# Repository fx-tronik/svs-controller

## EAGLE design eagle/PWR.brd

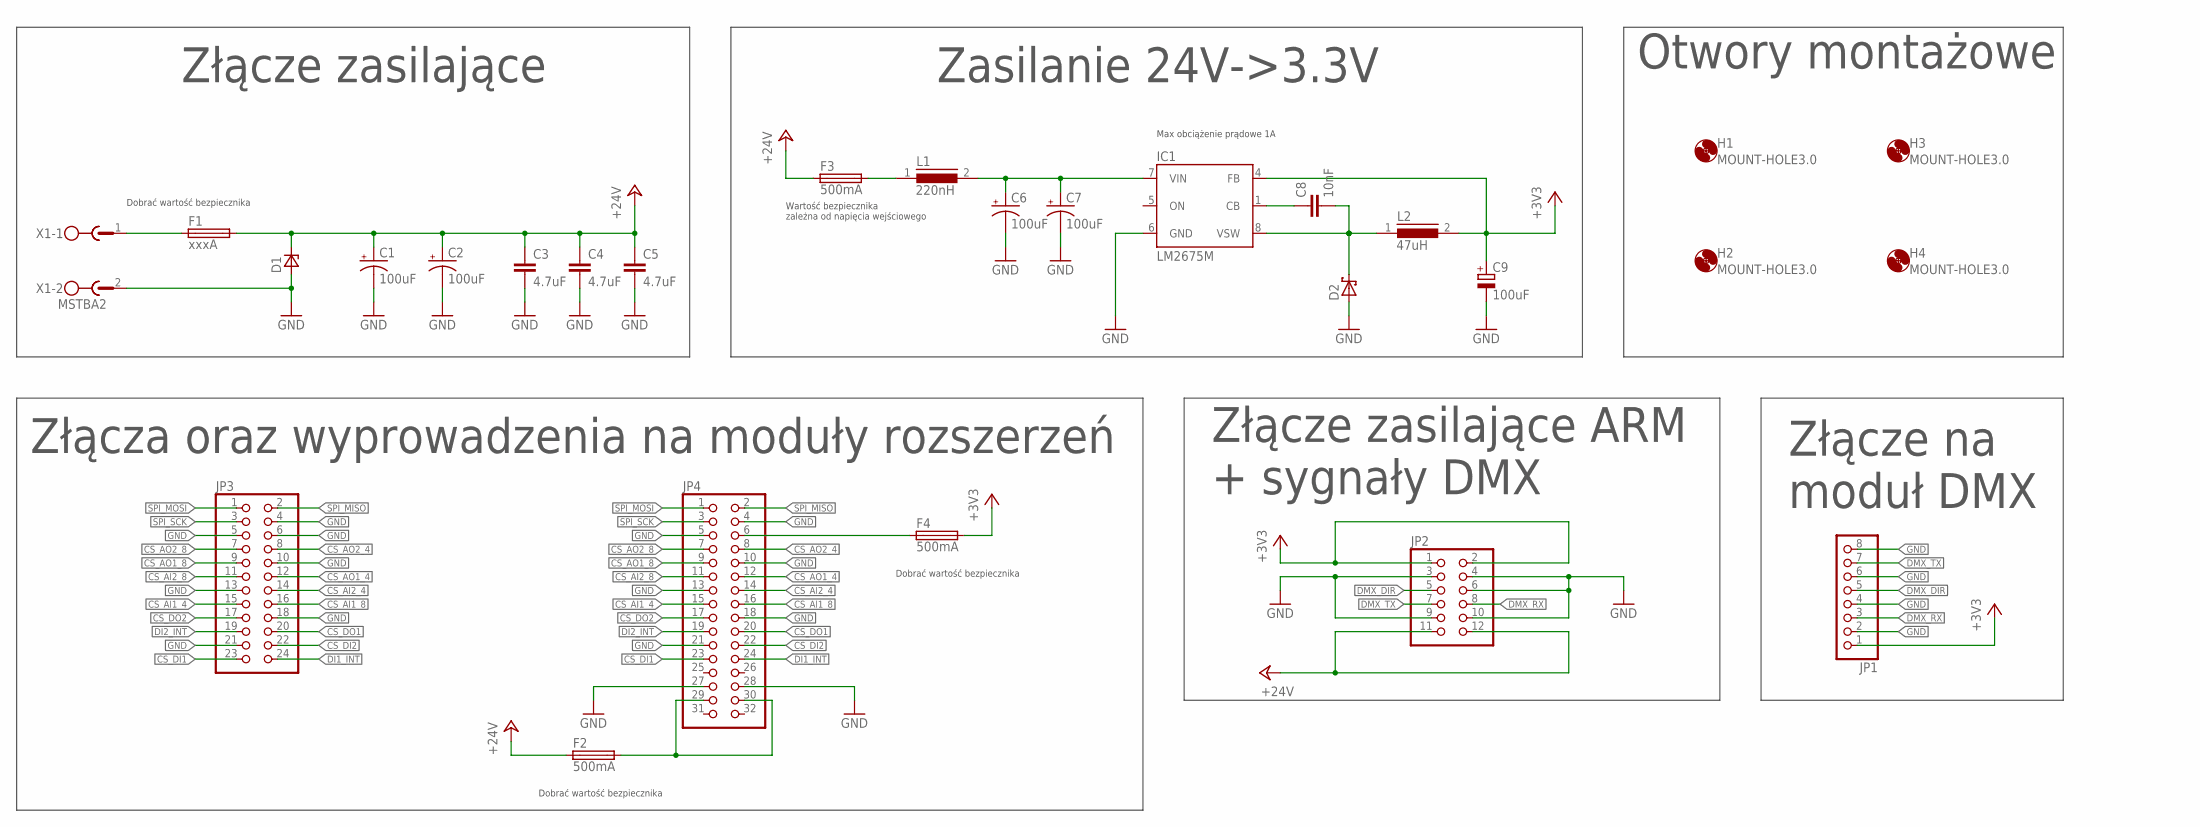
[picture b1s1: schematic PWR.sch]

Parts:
C1, C2, C6, C7: 100uF; TT5D10; MPN UPJ1H101MPD6
C3, C4, C5: 4.7uF; C0805; MPN GRM21BR61H475ME51L
C8: 10nF; C0603; MPN 06035C103KAT2A
C9: 100uF; SMC_C; MPN TAJC107K010TNJ
D1: P6SMB20A; SMB_A; MPN TPSMB24A-VR
D2: SCHOTTKY-DIODESMD; SMB; MPN SS26T3G
F1: xxxA; TR5; MPN 56000001009
F2, F3, F4: 500mA; TR5; MPN 56000001009
H1, H2, H3, H4: MOUNT-HOLE3.0; 3,0
IC1: LM2675M; SO08; MPN LM2675MX-3.3/NOPB
JP1: PINHD-1X8/90; 1X08/90; MPN DS1024-1*8R0
JP2: PINHD-2X6; 2X06; MPN DS1023-2*6S21
JP3: PINHD-2X12; 2X12; MPN DS1023-2*12S21
JP4: PINHD-2X16/90; 2X16/90; MPN DS1024-2*16R0
L1: 220nH; 7.3X6.3; MPN SRP7028A-R22Y
L2: 47uH; 12.5X12.5; MPN SRR1280-470M
X1: MSTBA2; MPN 2EDGRC-5.08-02P-14-00A(H)

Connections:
+3V3: C9.+, F4.2, IC1.4 (FB), JP1.1, JP2.1, JP2.2, L2.2
+24V: C1.+, C2.+, C3.1, C4.1, C5.1, D1.C, F1.2, F2.1, F3.1, JP2.11, JP2.12
CS_AI1_4: JP3.15, JP4.15
CS_AI1_8: JP3.16, JP4.16
CS_AI2_4: JP3.14, JP4.14
CS_AI2_8: JP3.11, JP4.11
CS_AO1_4: JP3.12, JP4.12
CS_AO1_8: JP3.9, JP4.9
CS_AO2_4: JP3.8, JP4.8
CS_AO2_8: JP3.7, JP4.7
CS_DI1: JP3.23, JP4.23
CS_DI2: JP3.22, JP4.22
CS_DO1: JP3.20, JP4.20
CS_DO2: JP3.17, JP4.17
DI1_INT: JP3.24, JP4.24
DI2_INT: JP3.19, JP4.19
DMX_DIR: JP1.5, JP2.5
DMX_RX: JP1.3, JP2.8
DMX_TX: JP1.7, JP2.7
GND: C1.-, C2.-, C3.2, C4.2, C5.2, C6.-, C7.-, C9.-, D1.A, D2.A, IC1.6 (GND), JP1.2, JP1.4, JP1.6, JP1.8, JP2.3, JP2.4, JP2.6, JP2.9, JP2.10, JP3.4, JP3.5, JP3.6, JP3.10, JP3.13, JP3.18, JP3.21, JP4.4, JP4.5, JP4.10, JP4.13, JP4.18, JP4.21, JP4.27, JP4.28, X1.2
unnamed: F1.1, X1.1
unnamed: F4.1, JP4.6
unnamed: F2.2, JP4.29, JP4.30
unnamed: F3.2, L1.1
unnamed: C8.1, IC1.1 (CB)
SPI_MISO: JP3.2, JP4.2
SPI_MOSI: JP3.1, JP4.1
SPI_SCK: JP3.3, JP4.3
VIN: C6.+, C7.+, IC1.7 (VIN), L1.2
VSW: C8.2, D2.C, IC1.8 (VSW), L2.1

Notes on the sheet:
Dobrać wartość bezpiecznika
Max obciążenie prądowe 1A
Wartość bezpiecznika zależna od napięcia wejściowego
Zasilanie 24V->3.3V
Złącze zasilające
Złącze na moduł DMX
Złącze zasilające ARM + sygnały DMX
Otwory montażowe
Złącza oraz wyprowadzenia na moduły rozszerzeń

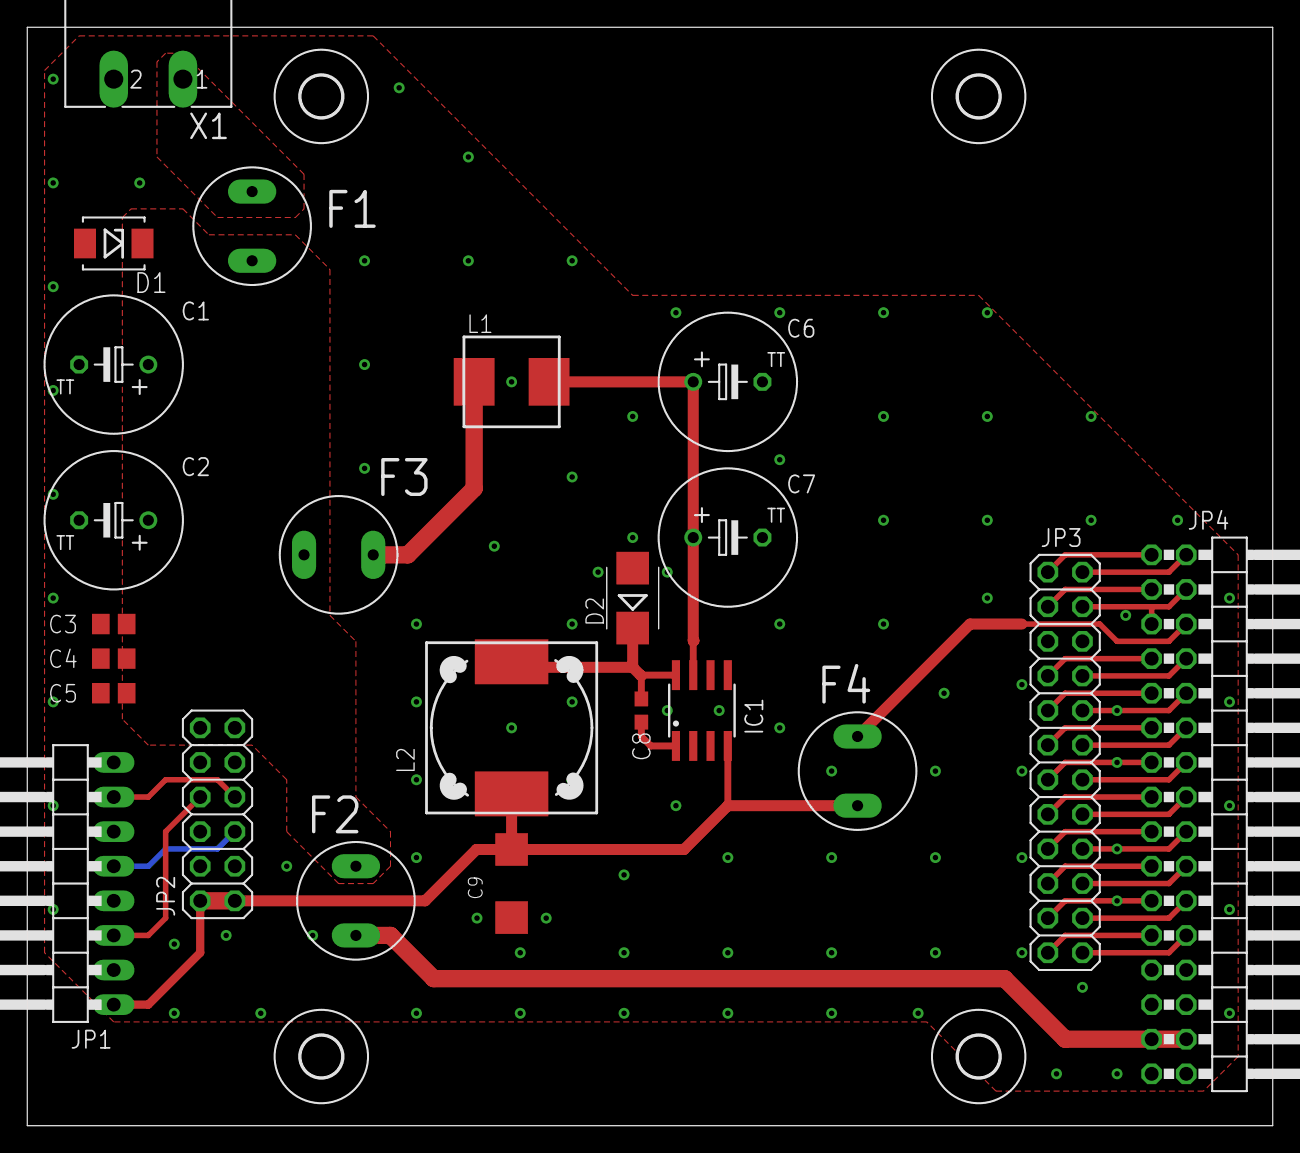
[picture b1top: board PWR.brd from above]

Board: 2 copper layers, 91.4 x 80.6 mm, 27 parts (0 on the bottom side), 30 nets.

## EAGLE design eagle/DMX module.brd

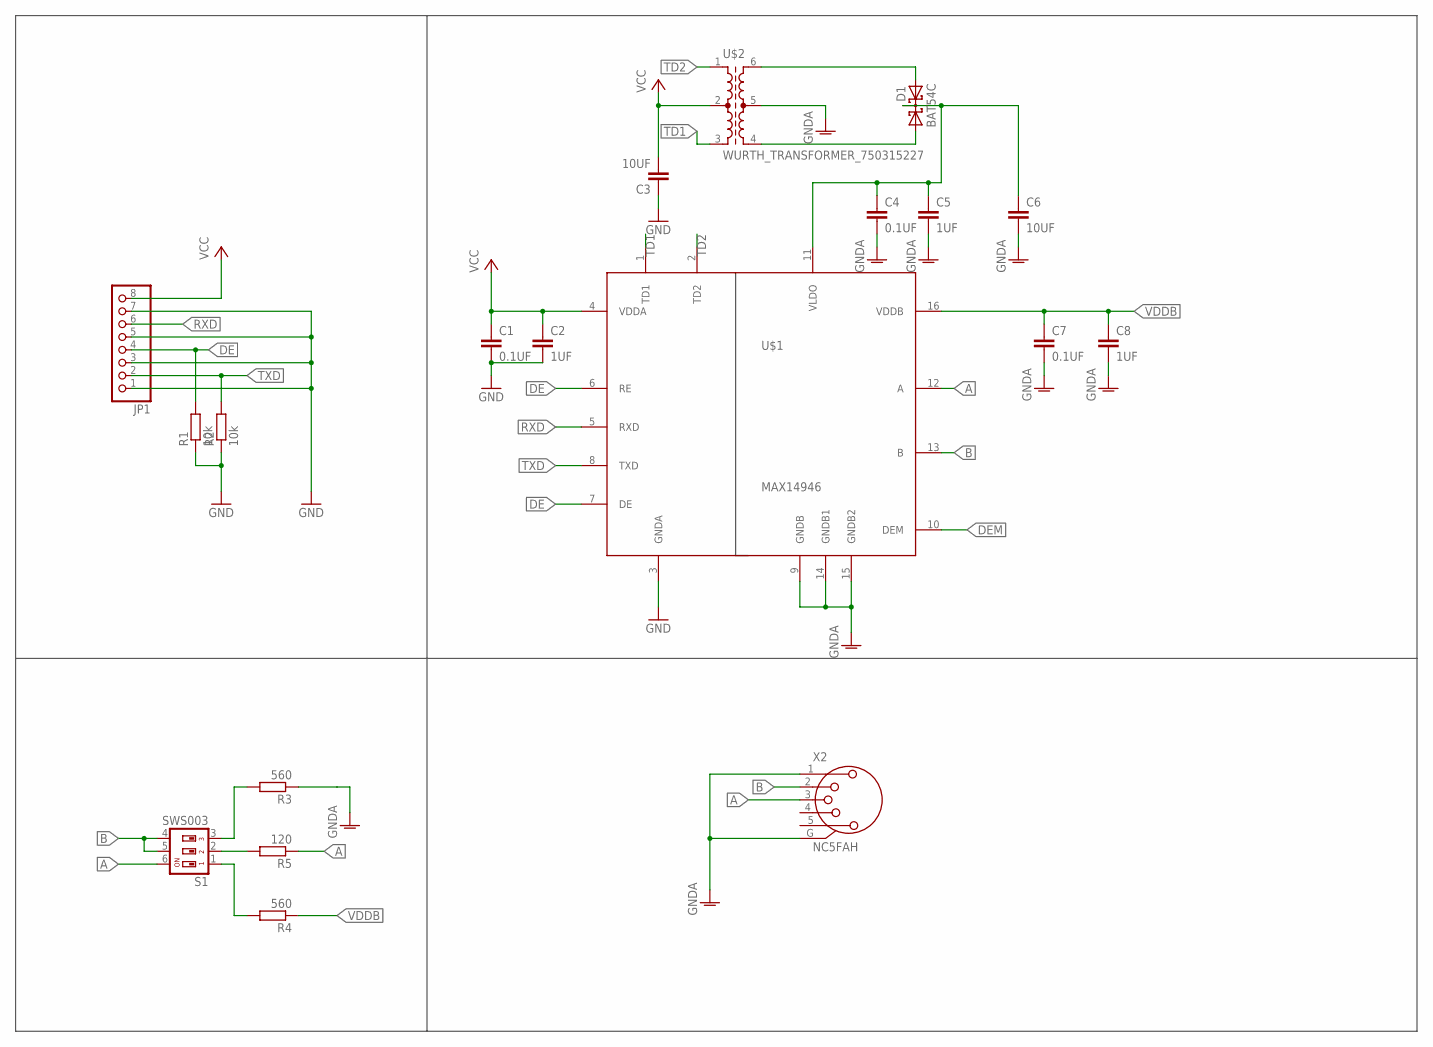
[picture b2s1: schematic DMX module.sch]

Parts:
C1, C4, C7: 0.1UF; C0603; MPN 06033C104KAT2A
C2, C5, C8: 1UF; C0603; MPN 0603YC105KAT4A
C3, C6: 10UF; C0805; MPN 08056G106ZAT2A
D1: BAT54C; SOT23; MPN 755-BAT54AHMFHT116
JP1: PINHD-1X8/90; 1X08/90; MPN DS1022-1*20RDF1-1
R1, R2: 10k; R0603; MPN RC0603JR-0710KA
R3, R4: 560; R0603; MPN RC0603FR-13560RL
R5: 120; R0603; MPN RC0603FR-10120RL
S1: SWS003; SMS-003; MPN 774-2193MST
U$1: MAX14946; SOIC16W; MPN 700-MAX14946EWE+
U$2: WURTH_TRANSFORMER_750315227; WURTH750315227; MPN 710-750315227
X2: NC5FAH

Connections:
A: R5.1, S1.6, U$1.12 (A), X2.3
B: S1.4, S1.5, U$1.13 (B), X2.2
DE: JP1.4, R1.2, U$1.6 (RE), U$1.7 (DE)
DEM: U$1.10 (DEM)
GND: C1.2, C2.2, C3.1, JP1.1, JP1.3, JP1.5, JP1.7, R1.1, R2.1, U$1.3 (GNDA)
GNDA: C4.2, C5.2, C6.2, C7.2, C8.2, R3.1, U$1.9 (GNDB), U$1.14 (GNDB1), U$1.15 (GNDB2), U$2.5, X2.1, X2.G
unnamed: R5.2, S1.2
unnamed: R4.2, S1.1
unnamed: D1.1 (A1), U$2.4
unnamed: D1.2 (A2), U$2.6
unnamed: C4.1, C5.1, C6.1, D1.3 (CC), U$1.11 (VLDO)
unnamed: R3.2, S1.3
RXD: JP1.6, U$1.5 (RXD)
TD1: U$1.1 (TD1), U$2.3
TD2: U$1.2 (TD2), U$2.1
TXD: JP1.2, R2.2, U$1.8 (TXD)
VCC: C1.1, C2.1, C3.2, JP1.8, U$1.4 (VDDA), U$2.2
VDDB: C7.1, C8.1, R4.1, U$1.16 (VDDB)

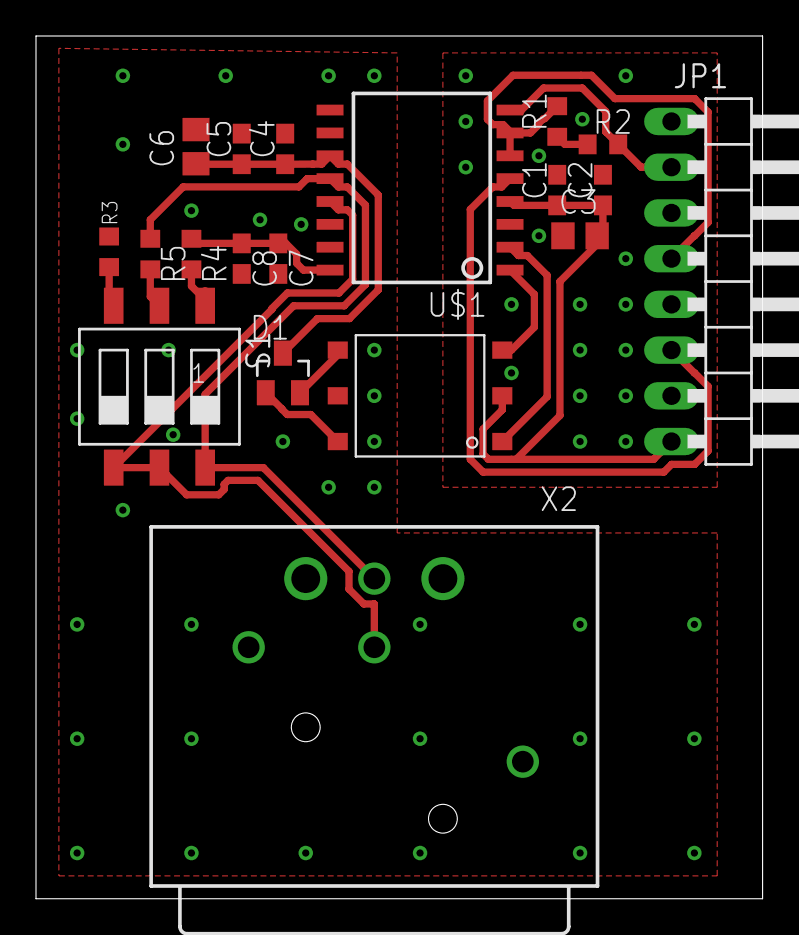
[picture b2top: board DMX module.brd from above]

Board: 2 copper layers, 40.4 x 47.9 mm, 19 parts (0 on the bottom side), 17 nets.

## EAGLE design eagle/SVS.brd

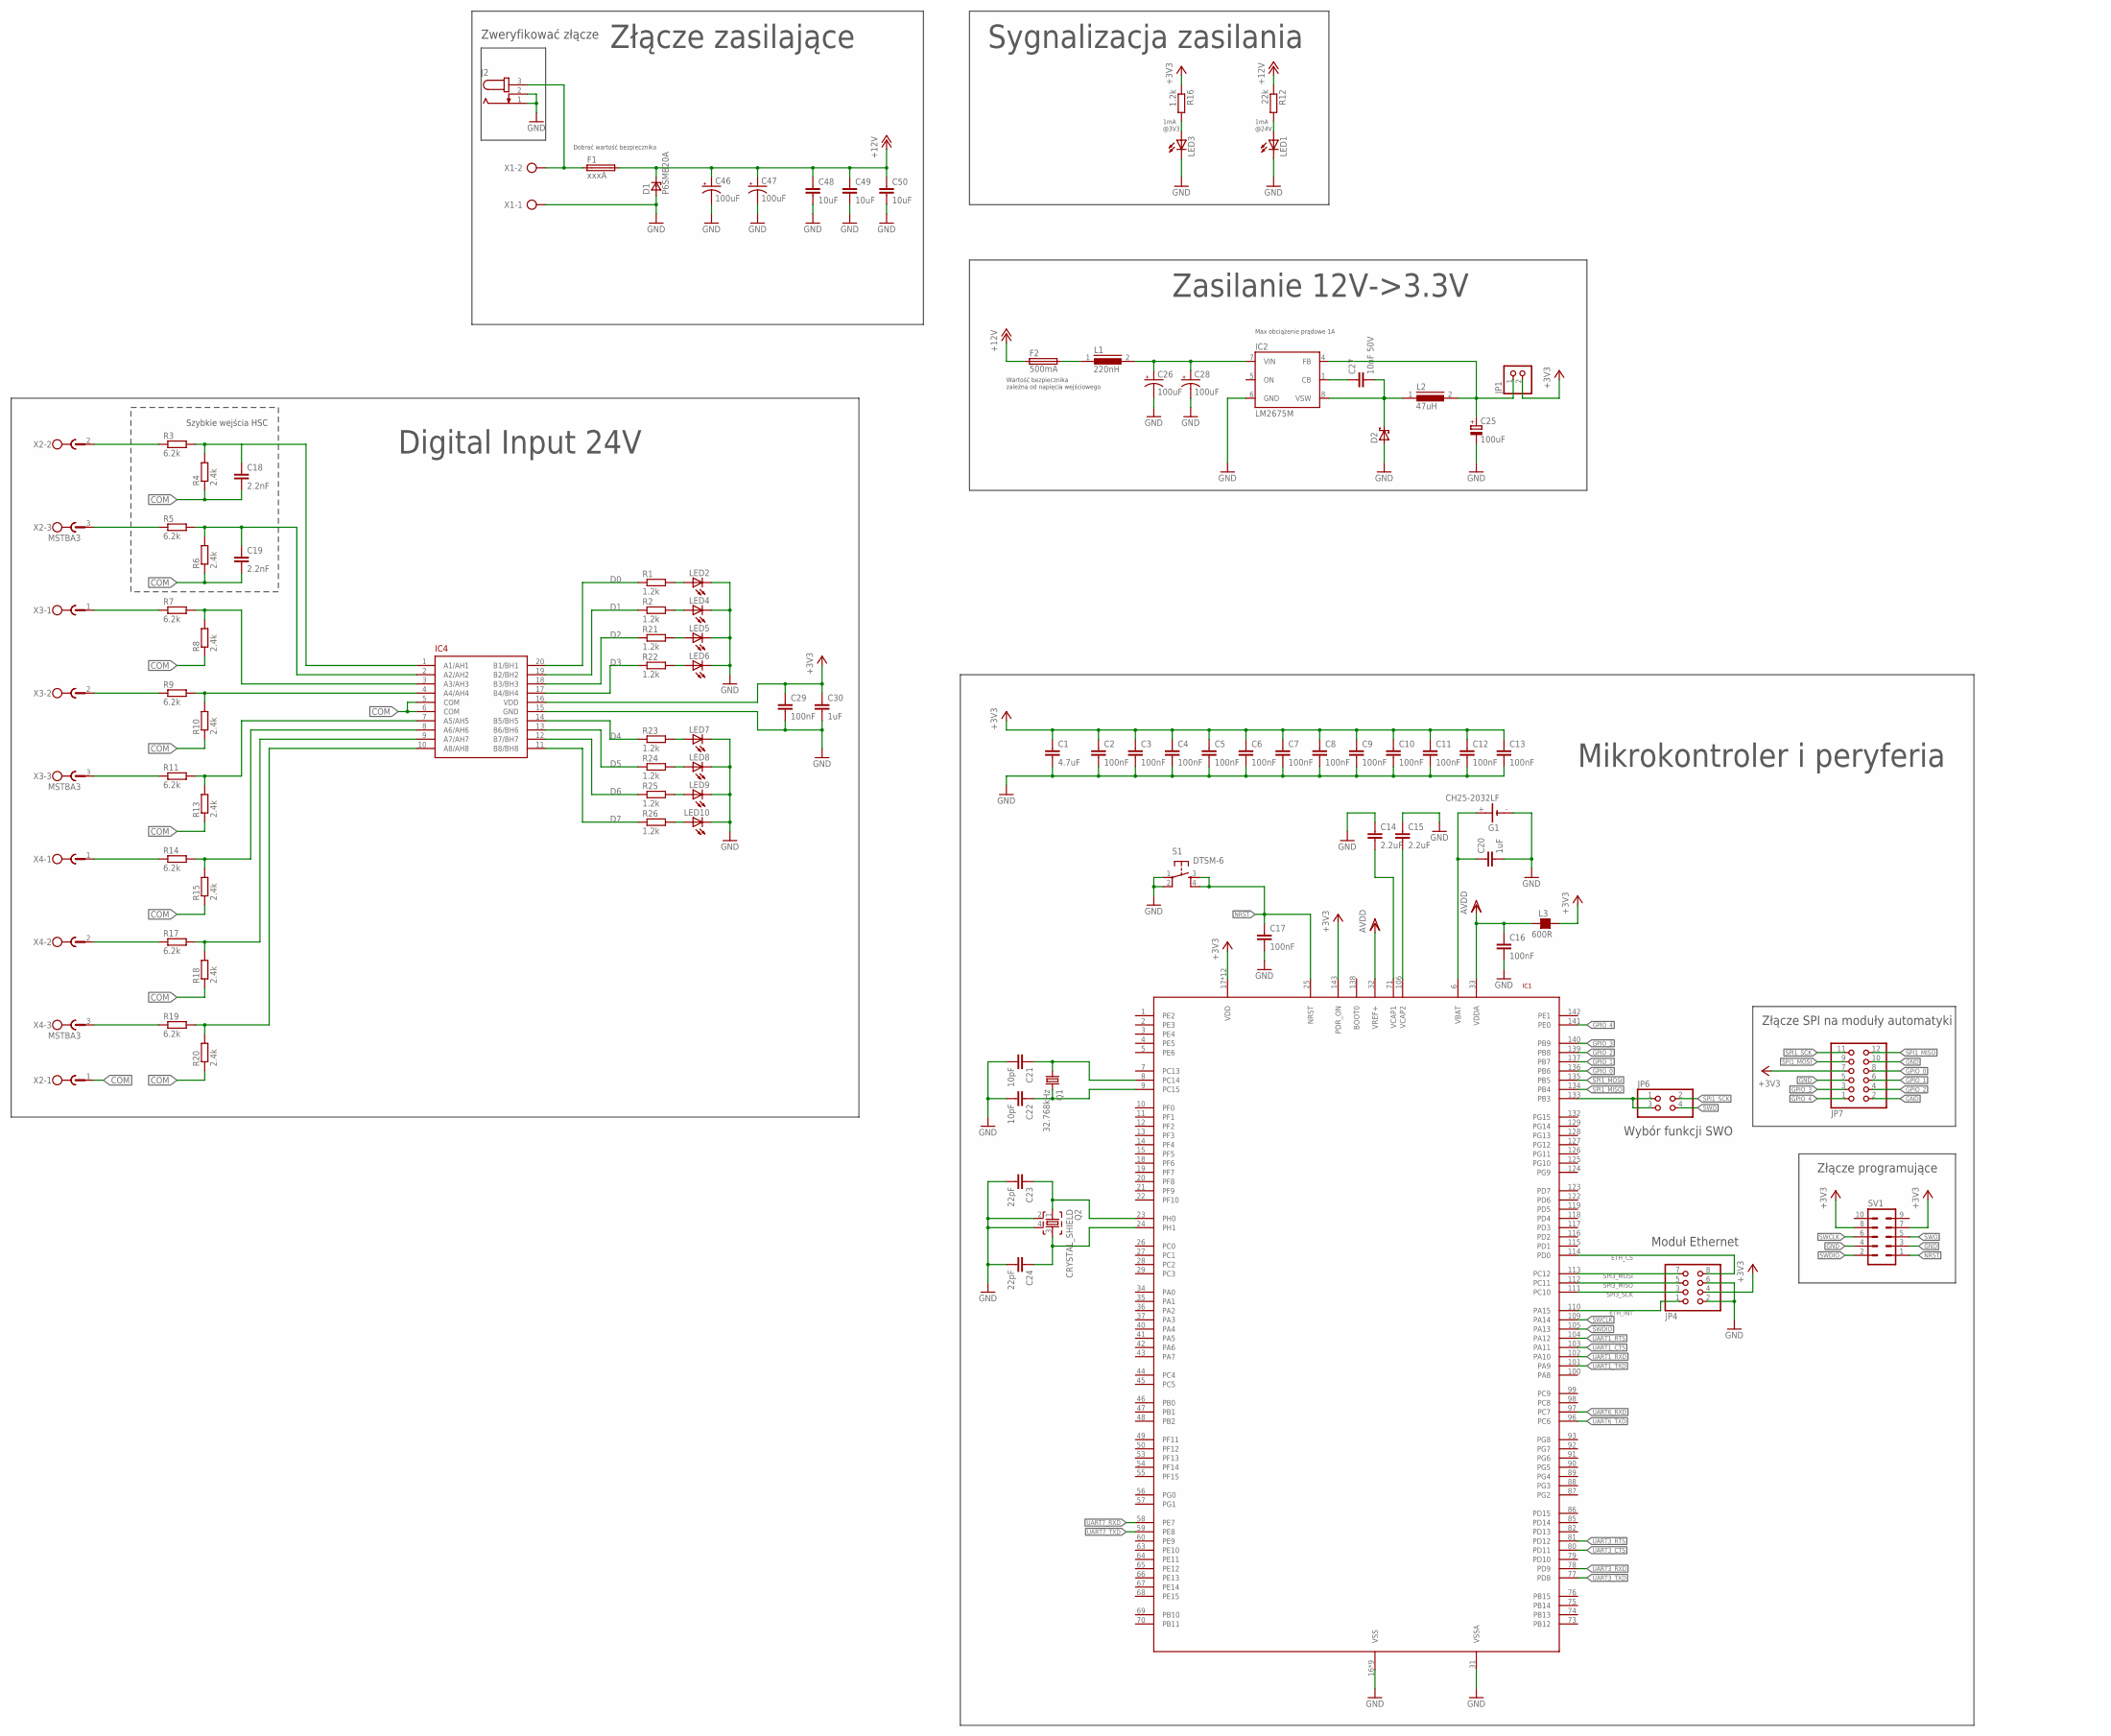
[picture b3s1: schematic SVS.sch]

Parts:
C1: 4.7uF; C0603K; MPN 0603ZD475KAT2A
C2, C3, C4, C5, C6, C7, C8, C9, C10, C11, C12, C13, C16, C17, C29: 100nF; C0603K; MPN 06033C104KAT2A
C14, C15: 2.2uF; C0603K; MPN 06036C225KAT2A
C18, C19: 2.2nF; C0805; MPN 06035C222JAT2A
C20, C30: 1uF; C0603K; MPN 0603YC105KAT4A
C21, C22: 10pF; C0603K; MPN 06035A100JAT2A
C23, C24: 22pF; C0603K; MPN 06035A220JAT2A
C25: 100uF; SMC_C; MPN TAJC107K010TNJ
C26, C28, C46, C47: 100uF; UD-8X10_NICHICON; MPN UCD1H101MNL1GS
C27: 10nF 50V; C0603; MPN 06035C103KAT2A
C48, C49, C50: 10uF; C0805; MPN GRM21BR6YA106KE43L
D1: P6SMB20A; SMB_A; MPN TPSMB24A-VR
D2: SCHOTTKY-DIODESMD; SMB; MPN SS26T3G
F1: xxxA; TR5
F2: 500mA; TR5
G1: CH25-2032LF; MPN CH25-2032
IC1: STM32F429ZILQFP144; LQFP144; MPN STM32F429ZIT6
IC2: LM2675M; SO08; MPN LM2675MX-3.3/NOPB
IC4: SI838X; QSOP-20; MPN SI8382P-IU
J2: JACK-PLUG1; SPC4078
JP1: PINHD-1X2; 1X02
JP4: PINHD-2X4; 2X04
JP6: PINHD-2X2; 2X02
JP7: PINHD-2X6/90; 2X06/90
L1: 220nH; 7.3X6.3; MPN SRP7028A-R22Y
L2: 47uH; 12.5X12.5; MPN SRR1280-470M
L3: 600R; L0603; MPN MMZ1608S601ATD25
LED1, LED3: LEDCHIP-LED0603; CHIP-LED0603; MPN APTD1608LSURCK
LED2, LED4, LED5, LED6, LED7, LED8, LED9, LED10: LEDCHIP-LED0603; CHIP-LED0603; MPN APTD1608LCGCK
Q1: 32.768kHz; CRYSTAL_3.5X1.5; MPN ECS-.327-9-34QCS-TR
Q2: CRYSTAL_SHIELD; CRYSTAL_5X3.2; MPN LFXTAL059158
R1, R2, R16, R21, R22, R23, R24, R25, R26: 1.2k; R0603; MPN RC0603FR-071K2L
R3, R5, R7, R9, R11, R14, R17, R19: 6.2k; R1206; MPN RC1206JR-076K2L
R4, R6, R8, R10, R13, R15, R18, R20: 2.4k; R1206; MPN RC1206JR-072K4L
R12: 22k; R0603; MPN RC0603FR-0722KL
S1: DTSM-6; MPN DTSM-63N-V-B
SV1: ML10
X1: AK300/2
X2, X3, X4: MSTBA3

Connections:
+3V3: C1.1, C2.1, C3.1, C4.1, C5.1, C6.1, C7.1, C8.1, C9.1, C10.1, C11.1, C12.1, C13.1, C29.1, C30.1, IC1.17 (VDD), IC1.30 (VDD), IC1.39 (VDD), IC1.52 (VDD), IC1.62 (VDD), IC1.72 (VDD), IC1.84 (VDD), IC1.95 (VDD), IC1.108 (VDD), IC1.121 (VDD), IC1.131 (VDD), IC1.143 (PDR_ON), IC1.144 (VDD), IC4.16 (VDD), JP1.2, JP4.4, JP7.7, L3.2, R16.1, SV1.7, SV1.8
+12V: C46.+, C47.+, C48.1, C49.1, C50.1, D1.C, F1.2, F2.1, R12.1
AVDD: IC1.32 (VREF+)
COM: C18.2, C19.2, IC4.5 (COM), IC4.6 (COM), R4.1, R6.1, R8.1, R10.1, R13.1, R15.1, R18.1, R20.1, X2.1
D0: IC4.20 (B1/BH1), R1.1
D1: IC4.19 (B2/BH2), R2.1
D2: IC4.18 (B3/BH3), R21.1
D3: IC4.17 (B4/BH4), R22.1
D4: IC4.14 (B5/BH5), R23.1
D5: IC4.13 (B6/BH6), R24.1
D6: IC4.12 (B7/BH7), R25.1
D7: IC4.11 (B8/BH8), R26.1
ETH_CS: IC1.114 (PD0), JP4.8
ETH_INT: IC1.110 (PA15), JP4.1
GND: C1.2, C2.2, C3.2, C4.2, C5.2, C6.2, C7.2, C8.2, C9.2, C10.2, C11.2, C12.2, C13.2, C14.1, C15.1, C16.2, C17.2, C20.2, C21.2, C22.2, C23.2, C24.2, C25.-, C26.-, C28.-, C29.2, C30.2, C46.-, C47.-, C48.2, C49.2, C50.2, D1.A, D2.A, G1.-, IC1.16 (VSS), IC1.31 (VSSA), IC1.38 (VSS), IC1.51 (VSS), IC1.61 (VSS), IC1.83 (VSS), IC1.94 (VSS), IC1.107 (VSS), IC1.120 (VSS), IC1.130 (VSS), IC2.6 (GND), IC4.15 (GND), J2.1, J2.2, JP4.2, JP4.6, JP7.2, JP7.5, JP7.10, LED1.C, LED2.C, LED3.C, LED4.C, LED5.C, LED6.C, LED7.C, LED8.C, LED9.C, LED10.C, Q2.2, Q2.4, S1.1, S1.2, SV1.3, SV1.4, X1.1
GPIO_0: IC1.136 (PB6), JP7.8
GPIO_1: IC1.137 (PB7), JP7.6
GPIO_2: IC1.139 (PB8), JP7.4
GPIO_3: IC1.140 (PB9), JP7.3
GPIO_4: IC1.141 (PE0), JP7.1
unnamed: F1.1, J2.3, X1.2
unnamed: C14.2, IC1.71 (VCAP1)
unnamed: C15.2, IC1.106 (VCAP2)
unnamed: C21.1, IC1.8 (PC14), Q1.1
unnamed: C22.1, IC1.9 (PC15), Q1.2
unnamed: IC1.133 (PB3), JP6.1, JP6.3
unnamed: C23.1, IC1.23 (PH0), Q2.1
unnamed: C24.1, IC1.24 (PH1), Q2.3
unnamed: C18.1, IC4.1 (A1/AH1), R3.2, R4.2
unnamed: F2.2, L1.1
unnamed: LED2.A, R1.2
unnamed: C19.1, IC4.2 (A2/AH2), R5.2, R6.2
unnamed: LED4.A, R2.2
unnamed: LED5.A, R21.2
unnamed: R3.1, X2.2
unnamed: C27.1, IC2.1 (CB)
unnamed: LED6.A, R22.2
unnamed: R5.1, X2.3
unnamed: IC4.3 (A3/AH3), R7.2, R8.2
unnamed: R7.1, X3.1
unnamed: IC4.4 (A4/AH4), R9.2, R10.2
unnamed: R9.1, X3.2
unnamed: IC4.7 (A5/AH5), R11.2, R13.2
unnamed: R11.1, X3.3
unnamed: IC4.8 (A6/AH6), R14.2, R15.2
unnamed: R14.1, X4.1
unnamed: IC4.9 (A7/AH7), R17.2, R18.2
unnamed: R17.1, X4.2
unnamed: IC4.10 (A8/AH8), R19.2, R20.2
unnamed: R19.1, X4.3
unnamed: LED1.A, R12.2
unnamed: LED7.A, R23.2
unnamed: LED8.A, R24.2
unnamed: LED9.A, R25.2
unnamed: LED10.A, R26.2
unnamed: C25.+, IC2.4 (FB), JP1.1, L2.2
unnamed: LED3.A, R16.2
NRST: C17.1, IC1.25 (NRST), S1.3, S1.4, SV1.1
SPI1_MISO: IC1.134 (PB4), JP7.12
SPI1_MOSI: IC1.135 (PB5), JP7.9
SPI1_SCK: JP6.2, JP7.11
SPI3_MISO: IC1.112 (PC11), JP4.5
SPI3_MOSI: IC1.113 (PC12), JP4.7
SPI3_SCK: IC1.111 (PC10), JP4.3
SWCLK: IC1.109 (PA14), SV1.6
SWDIO: IC1.105 (PA13), SV1.2
SWO: JP6.4, SV1.5
UART1_CTS: IC1.103 (PA11)
UART1_RTS: IC1.104 (PA12)
UART1_RXD: IC1.102 (PA10)
UART1_TXD: IC1.101 (PA9)
UART3_CTS: IC1.80 (PD11)
UART3_RTS: IC1.81 (PD12)
UART3_RXD: IC1.78 (PD9)
UART3_TXD: IC1.77 (PD8)
UART6_RXD: IC1.97 (PC7)
UART6_TXD: IC1.96 (PC6)
UART7_RXD: IC1.58 (PE7)
UART7_TXD: IC1.59 (PE8)
VBAT: C20.1, G1.+, IC1.6 (VBAT)
VDD: C16.1, IC1.33 (VDDA), L3.1
VIN: C26.+, C28.+, IC2.7 (VIN), L1.2
VSW: C27.2, D2.C, IC2.8 (VSW), L2.1

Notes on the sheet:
Dobrać wartość bezpiecznika
Max obciążenie prądowe 1A
Wartość bezpiecznika zależna od napięcia wejściowego
Zasilanie 12V->3.3V
Mikrokontroler i peryferia
Sygnalizacja zasilania
Zweryfikować złącze
Złącze zasilające
1mA @3V3
Moduł Ethernet
Złącze programujące
Złącze SPI na moduły automatyki
Wybór funkcji SWO
Digital Input 24V
Szybkie wejścia HSC
1mA @24V

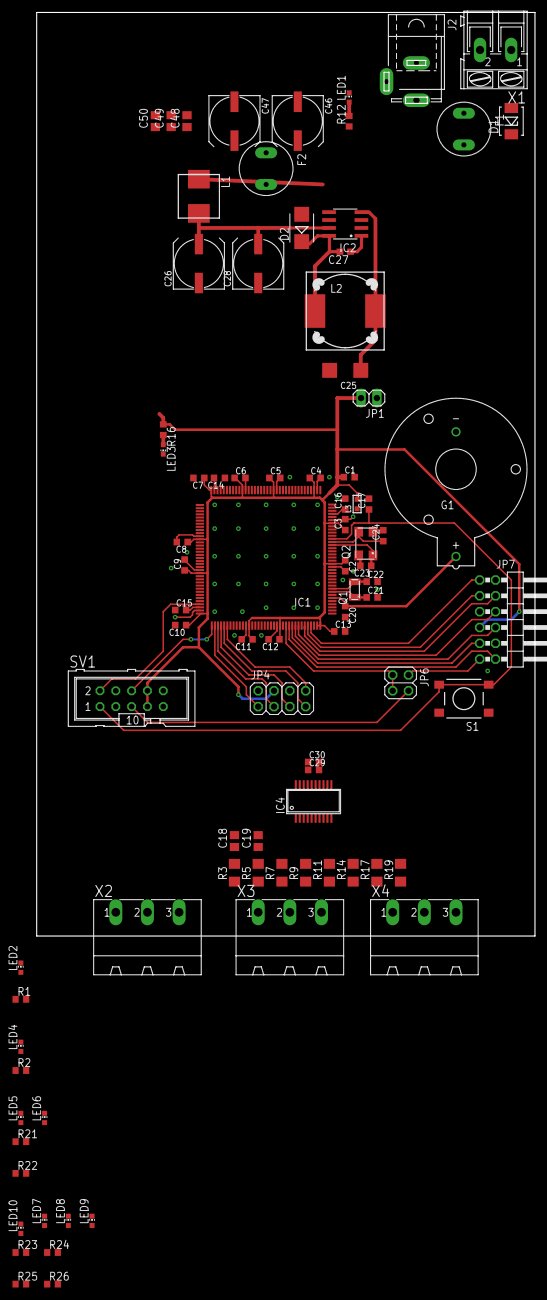
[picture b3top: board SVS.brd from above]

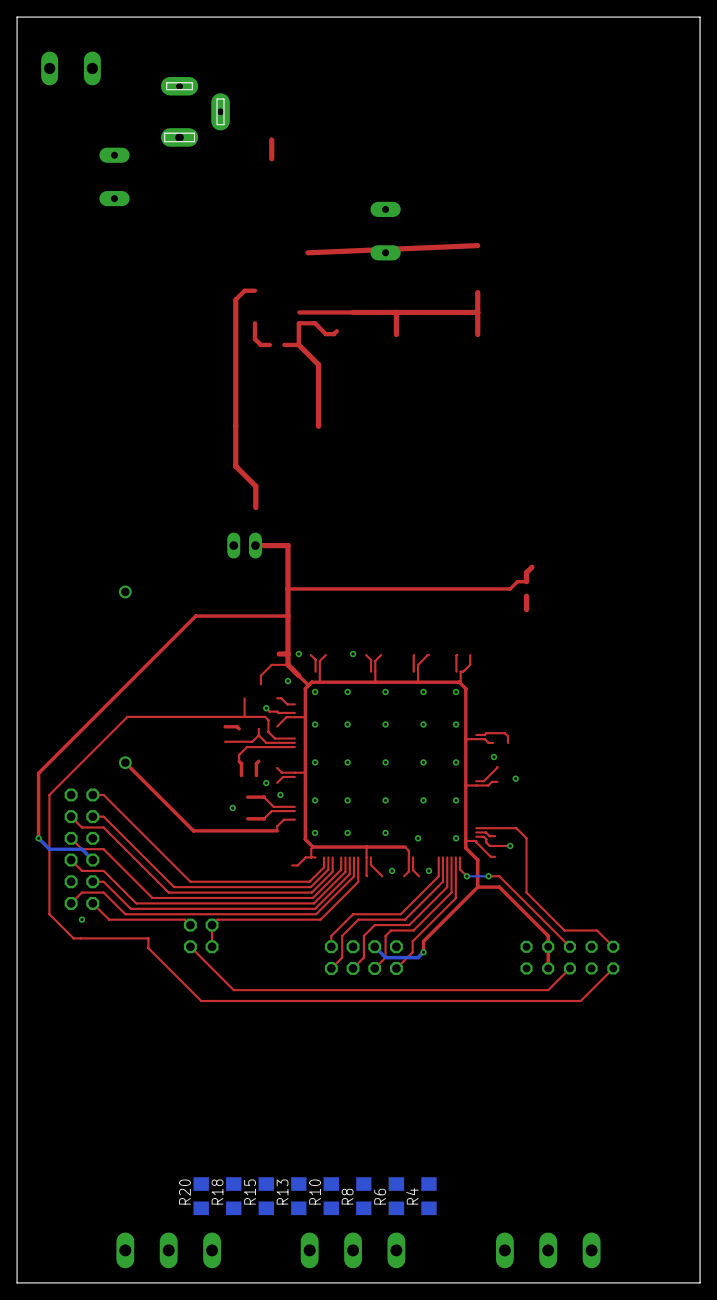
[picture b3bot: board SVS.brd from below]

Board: 2 copper layers, 80.0 x 148.3 mm, 95 parts (8 on the bottom side), 70 nets.

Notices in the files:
parts and their libraries:
rc-master-smd: Copyright (C) 2007, Bob Starr
